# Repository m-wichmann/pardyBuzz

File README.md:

# pardyBuzz
This is a little hardware, that attaches a button to USB using an ATtiny. Instead of hardware USB this project uses the software USB stack V-USB [1]. Basically the whole project is based on the info from the V-USB site.

This project is developed as input for the pyPardy project [2].

# License
The firmware is licensed under GPLv3. The hardware is licensed under TAPR Open Hardware License.

[1] http://www.obdev.at/vusb/
[2] https://github.com/wichmann/pyPardy

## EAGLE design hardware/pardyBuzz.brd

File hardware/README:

# pardyBuzz Hardware
This is a simple PCB that contains a ATtiny and the USB interface. A button should be soldered to the PB2 pin, since thats the interrupt pin.

# BOM
* 1x ATtiny25/45/85 (tested with ATtiny85)
* 1x 100 nF
* 2x 68 Ohm
* 1x 1.5K Ohm
* 2x 3.6 V Zener Diode

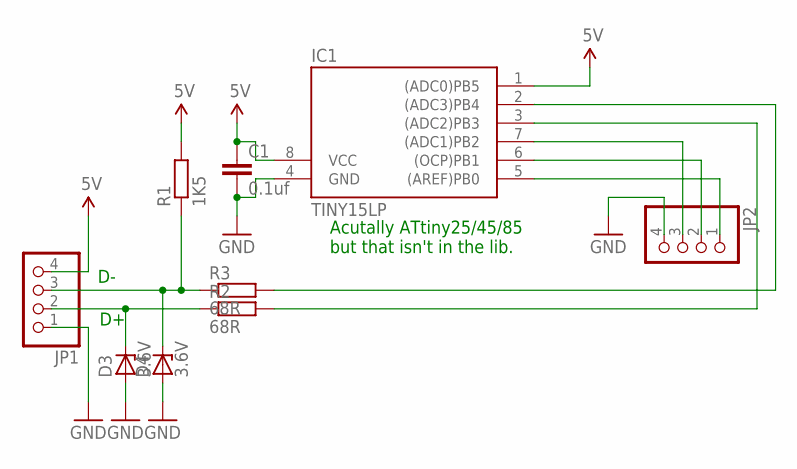
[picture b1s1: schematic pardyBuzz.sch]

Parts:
C1: 0.1uf; C050-024X044
D3, D4: 3.6V; DO34Z7
IC1: TINY15LP; DIL08
JP1, JP2: PINHD-1X4; 1X04
R1: 1K5; 0204V
R2, R3: 68R; 0204V

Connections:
5V: C1.1, IC1.1 ((ADC0)PB5), IC1.8 (VCC), JP1.4, R1.2
GND: C1.2, D3.A, D4.A, IC1.4 (GND), JP1.1, JP2.4
unnamed: IC1.3 ((ADC2)PB3), R2.2
unnamed: D4.C, JP1.3, R1.1, R3.1
unnamed: D3.C, JP1.2, R2.1
unnamed: IC1.7 ((ADC1)PB2), JP2.3
unnamed: IC1.6 ((OCP)PB1), JP2.2
unnamed: IC1.2 ((ADC3)PB4), R3.2
unnamed: IC1.5 ((AREF)PB0), JP2.1

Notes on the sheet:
Acutally ATtiny25/45/85 but that isn't in the lib.

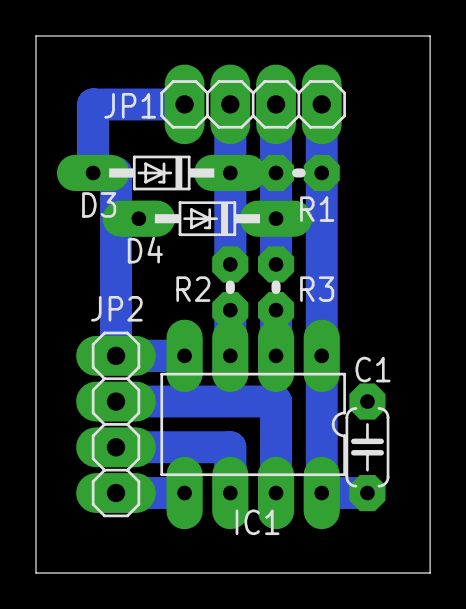
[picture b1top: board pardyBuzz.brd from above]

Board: 2 copper layers, 21.9 x 29.8 mm, 9 parts (0 on the bottom side), 9 nets.

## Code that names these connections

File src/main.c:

#include <avr/interrupt.h>
#include <avr/eeprom.h>
#include <util/delay.h>
#include "usbdrv.h"
#include "osc_cal.h"

/*
 * TOOD:
 * - Watchdog? Brownout?
 */

/*
 * PB0: MOSI (ISP)
 * PB1: MISO (ISP)
 * PB2: SCK (ISP) / Button
 * PB3: D-
 * PB4: D+
 * PB5: RESET (ISP)
 */

#define EEPROM_ADDR_DEVICE_ID       ((uint8_t *) 1)
uint8_t device_id = 0x00;

usbMsgLen_t usbFunctionSetup(uchar data[8])
{
    usbRequest_t *rq = (void *)data;
    static uchar replyBuf[1];

    usbMsgPtr = (usbMsgPtr_t) replyBuf;
    if(rq->bRequest == 0){      /* Get/Set Device ID */
        /* Reserved id 0x00 is used to just read the id.
         * All other values set the device id.
         */
        if (rq->wValue.bytes[0] != 0x00)
        {
            device_id = rq->wValue.bytes[0]; 
        	eeprom_update_byte(EEPROM_ADDR_DEVICE_ID, device_id);
        }
        replyBuf[0] = device_id;
        return 1;
    }

    return 0;
}


/**
 * Button interrupt.
 * Debouncing is realized through USB (poll interval 25ms).
 * Everything else can be done later in software.
 */
ISR (INT0_vect)
{
    static uchar data[1] = {0xa5};  /* marker 0xa5 to detect transmission problems. */

    /* Just update the interrupt data, regardless of current transferstate.
     * Either the data is overwritten, or another interrupt is send.
     */
    usbSetInterrupt(data, 1);

    GIMSK |= (1 << INTF0);
}



int main(void)
{
    /* read device id */
    device_id = eeprom_read_byte(EEPROM_ADDR_DEVICE_ID);

    /* Button with pull up */
    DDRB  &= ~(1 << PB2);
    PORTB |=  (1 << PB2);

    /* Some flank interrupt of the button. */
    MCUCR &= ~(1 << ISC00);
    MCUCR |= (1 << ISC01);
    GIMSK |= (1 << INTF0);

    usbInit();

    usbDeviceDisconnect();
    _delay_ms(500.0);
    usbDeviceConnect();

    sei();

    for(;;){    /* main event loop */
        usbPoll();
    }

    return 0;
}

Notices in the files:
parts and their libraries:
SparkFun: Licensing: CC v3.0 Share-Alike You are welcome to use this library for commercial purposes.
